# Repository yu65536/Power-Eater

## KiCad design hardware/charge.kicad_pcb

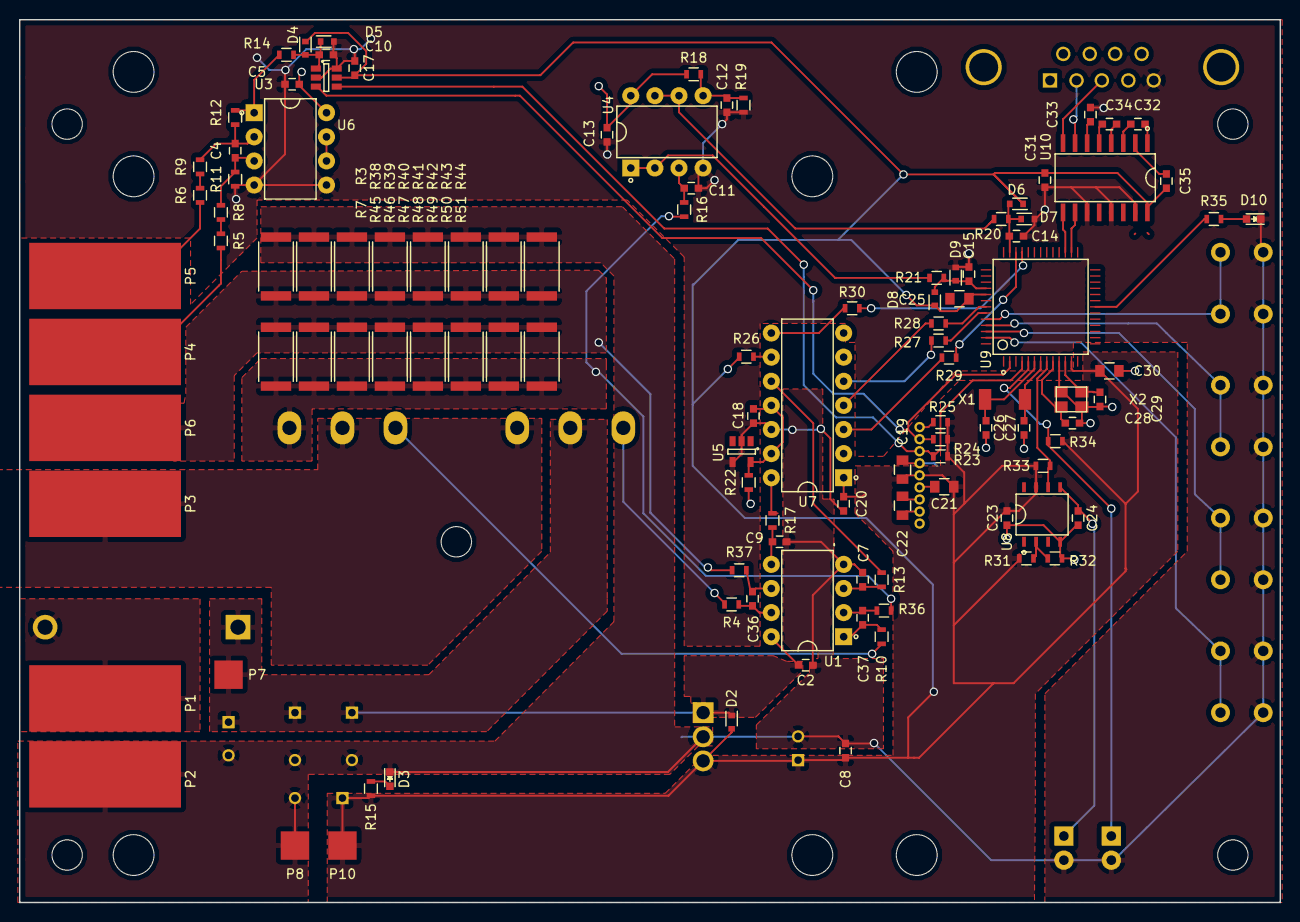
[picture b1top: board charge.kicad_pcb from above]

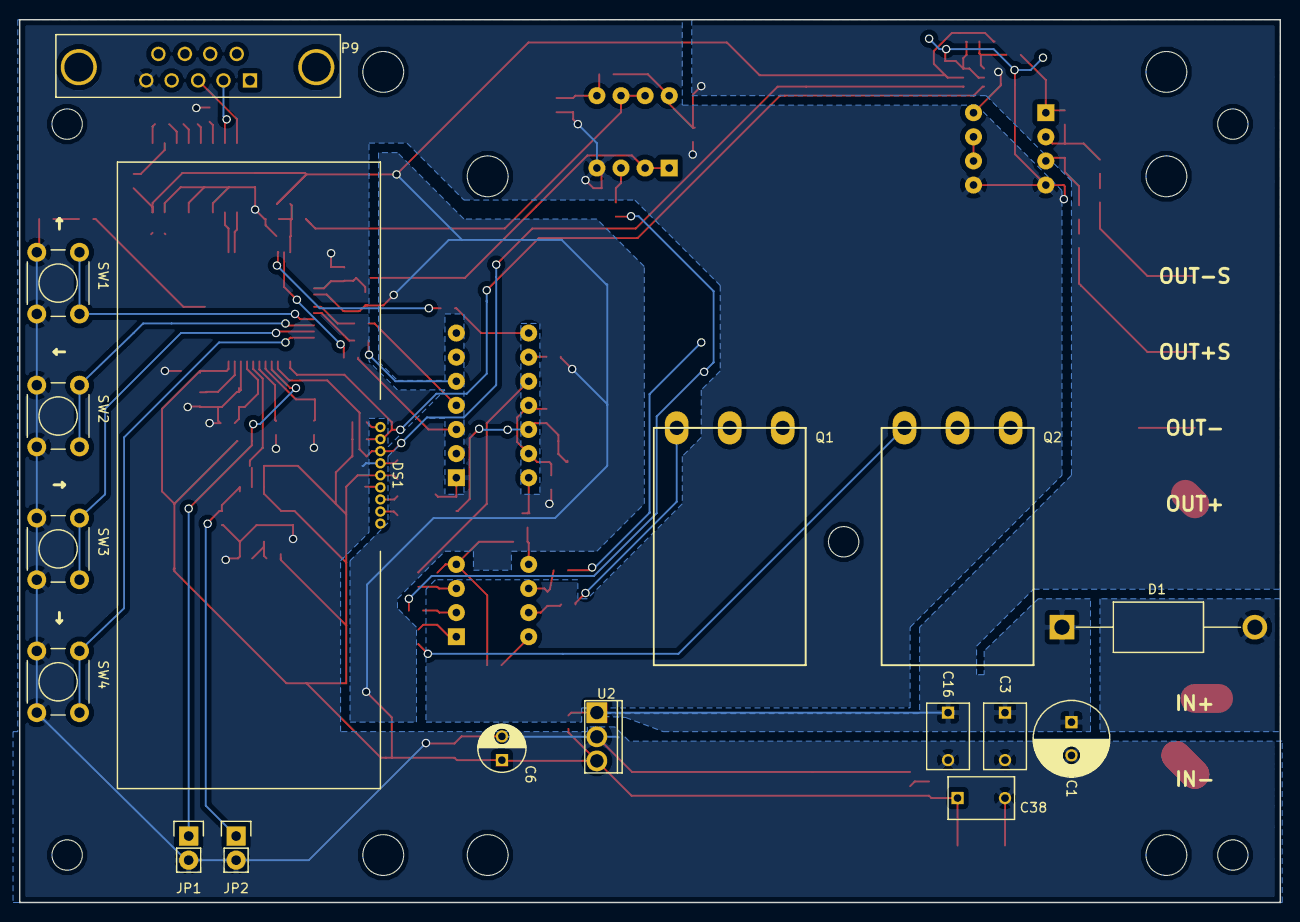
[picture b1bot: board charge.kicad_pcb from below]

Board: 2 copper layers, 132.8 x 93.0 mm, 128 parts (17 on the bottom side), 73 nets.

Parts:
C1: 470u; C_Radial_D8_L11.5_P3.5
C2, C4, C5, C7, C8, C9, C10, C11, C12, C13, C14, C15, C17, C18, C20, C23, C24, C31, C32, C33, C34, C35: 0.1u; C_0603
C3, C16, C38: 47u; C_Rect_L7_W4.5_P5
C6: 47u; C_Radial_D5_L11_P2.5
C19, C21, C22, C25, C30: 1u; C_0805
C26, C27: 22p; C_0603
C28, C29: 18p; C_0603
C36, C37: 0.01u; C_0603
D1: SBM1045VSS
D2, D4, D5, D6, D7, D8, D9: RB751S-40; SOD-523
D3, D10: LED; LED_0603
DS1: AQM1602A
JP1, JP2: JUMPER; Pin_Header_Straight_1x02
P1, P2, P3, P4, P5, P6: BH-6-15
P7, P8, P10: BH-6-15; pad-3-3
P9: CONN_01X09; DB9MD
Q1, Q2: 2SD2390; TO-247_PadsOnly_Neutral123
R3, R7, R38, R39, R40, R41, R42, R43, R44, R45, R46, R47, R48, R49, R50, R51: 1; R_2512
R4, R10: 1k; R_0603
R5, R6, R8, R9, R18, R22: 20k; R_0603
R11, R12, R19, R23, R24, R25, R26, R31, R32, R36, R37: 10k; R_0603
R13, R17: 0; R_0603
R14, R16, R20, R21, R27, R28, R29, R30: 100; R_0603
R15, R35: 470; R_0603
R33, R34: 4.7k; R_0603
SW1, SW2, SW3, SW4: SW_PUSH; SW_PUSH_6mm
U1, U3, U4: NJM2119; NJM2119D
U2: LM2940; LM2940CT-5.0
U5: NJM2825; SOT-23-5
U6: MCP3425A0T-E/CH; SOT-23-6
U7: MCP4922-E/P; MCP4922-E_P
U8: M51957BFP; M51957B
U9: R5F21256SNFP
U10: ADM3202ARN
X1: FC-255 32.768kHz; FC-255
X2: FA-238 20MHz; crystal_FA238-TSX3225

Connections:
+5V: C6.1, C8.1, C17.1, C19.2, C20.1, C21.2, C23.1, C25.1, C30.1, C31.1, C35.1, C38.1, D2.2, D4.1, D6.1, D8.1, DS1.5, P10.1, R15.2, R22.1, R23.1, R24.1, R25.1, R26.1, R31.1, R33.1, R34.1, U2.3, U6.5, U7.1, U8.7, U9.12, U9.44, U10.16
AD: C10.1, D4.2, D5.1, R14.1, U6.1
CS: R29.1, U9.37
DA1: R17.1, U7.14
DA2: R13.1, U7.10
GND: C1.2, C2.2, C3.2, C5.2, C6.2, C7.2, C8.2, C9.2, C10.2, C11.2, C12.2, C13.2, C14.2, C15.2, C16.2, C17.2, C18.2, C19.1, C20.2, C23.2, C24.2, C25.2, C26.2, C27.1, C28.2, C29.1, C30.2, C31.2, C33.2, C38.2, D3.1, D5.2, D7.2, D9.2, D10.1, DS1.4, JP1.2, JP2.2, P2.1, P8.1, P9.5, R3.2, R11.1, R19.1, R32.2, R38.2, R39.2, R40.2, R41.2, R42.2, R43.2, R44.2, SW1.1, SW2.1, SW3.1, SW4.1, U1.4, U2.2, U3.4, U3.5, U4.4, U5.2, U5.4, U6.2, U6.6, U7.12, U8.4, U9.10, U10.11, U10.13, U10.15, X2.3
I2C_SCL: DS1.2, R24.2, U6.3, U9.2
I2C_SDA: DS1.3, R23.2, U6.4, U9.4
LDAC: R30.1, U9.36
unnamed: C4.1, R8.1, R11.2, U3.3
unnamed: C4.2, R9.1, R12.2, U3.2
unnamed: C7.1, R13.2, U1.3
unnamed: C9.1, R17.2, U1.5
unnamed: C11.1, R16.1, U4.3
unnamed: C12.1, R18.1, R19.2, U4.5
unnamed: C18.1, R22.2, U5.5, U7.11, U7.13
unnamed: C21.1, DS1.6
unnamed: C22.1, DS1.8
unnamed: C22.2, DS1.7
unnamed: C24.1, JP2.1, U8.5
unnamed: C26.1, U9.6, X1.1
unnamed: C27.2, U9.7, X1.2
unnamed: C28.1, U9.9, X2.1
unnamed: C29.2, U9.11, X2.2
unnamed: C32.1, U10.1
unnamed: C32.2, U10.3
unnamed: C33.1, U10.6
unnamed: C34.1, U10.4
unnamed: C34.2, U10.5
unnamed: C35.2, U10.2
unnamed: C36.1, R37.2, U1.6
unnamed: C36.2, R4.1, U1.7
unnamed: C37.1, R36.1, U1.2
unnamed: C37.2, R10.1, U1.1
unnamed: D1.2, P1.1
unnamed: D3.2, R15.1
unnamed: D10.2, R35.2
unnamed: DS1.1, R25.2
unnamed: JP1.1, R34.2, U9.5
unnamed: P3.1, Q1.3, Q2.2
unnamed: P4.1, R5.2
unnamed: P5.1, R6.2
unnamed: P6.1, R3.1, R7.2, R37.1, R38.1, R39.1, R40.1, R41.1, R42.1, R43.1, R44.1, R45.2, R46.2, R47.2, R48.2, R49.2, R50.2, R51.2
unnamed: P9.2, U10.7
unnamed: P9.3, U10.8
unnamed: Q1.1, R4.2
unnamed: Q2.1, R10.2
unnamed: Q2.3, R7.1, R16.2, R36.2, R45.1, R46.1, R47.1, R48.1, R49.1, R50.1, R51.1
unnamed: R5.1, R8.2
unnamed: R6.1, R9.2
unnamed: R12.1, R14.2, U3.1
unnamed: R20.2, U4.6, U4.7
unnamed: R21.2, U4.1, U4.2
unnamed: R26.2, U7.9
unnamed: R27.2, U7.5
unnamed: R28.2, U7.4
unnamed: R29.2, U7.3
unnamed: R30.2, U7.8
unnamed: R31.2, R32.1, U8.2
unnamed: R33.2, U8.6, U9.8
unnamed: R35.1, U9.20
unnamed: SW1.2, U9.48
unnamed: SW2.2, U9.49
unnamed: SW3.2, U9.50
unnamed: SW4.2, U9.51
unnamed: U3.6, U3.7
unnamed: U9.29, U10.9
unnamed: U9.28, U10.10
SCK: R28.1, U9.46
SDI: R27.1, U9.47
VCC: C1.1, C2.1, C3.1, C5.1, C13.1, C16.1, D1.1, D2.1, P7.1, Q1.2, R18.2, U1.8, U2.1, U3.8, U4.8
bat_moni: C14.1, D6.2, D7.1, R20.1, U9.38
i_moni: C15.1, D8.2, D9.1, R21.1, U9.43

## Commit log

2017-08-16 commit test
2017-08-16 first software commit
2017-08-16 first hardware commit
2017-08-16 some file added
2017-08-16 readme write
2017-08-16 discharge data
2017-08-17 circult update
2017-08-17 todo write
2017-08-17 bat life image add
2017-09-01 ext-io add
2017-09-01 hardware change
